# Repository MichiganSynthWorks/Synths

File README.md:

# Synths
Synth Related Projects

Bella: Synth based on the Mutable Instruments Anushri originally designed by Emilie Gillet

Xena: Synth based on the Mutable Instruments Ambika originally designed by Emilie Gillet

MIDIme: MIDI processor based on the Mutable Instruments MIDIpal originally designed by Emilie Gillet

UMR2 CSO1 Edition: Cusomized MIDI to keyboard adapter for the Yamaha CS-01.  UMR2 Orginally designed by John Staskevich

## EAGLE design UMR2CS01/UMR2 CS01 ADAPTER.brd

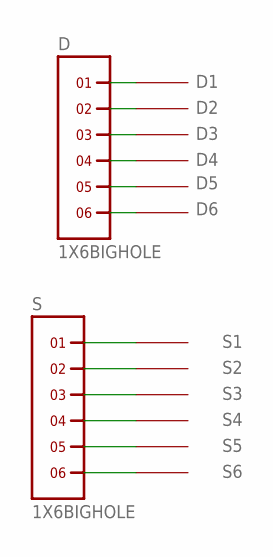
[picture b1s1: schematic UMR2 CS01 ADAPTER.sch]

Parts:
D: 1X6BIGHOLE; 1X6
D1, D2, D3, D4, D5, D6: SMD_PAD; SMDPAD_1X2
S: 1X6BIGHOLE; 1X6
S1, S2, S3, S4, S5, S6: SMD_PAD; SMDPAD_1X2

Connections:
unnamed: D.1, D1.P$1
unnamed: D.2, D2.P$1
unnamed: D.3, D3.P$1
unnamed: D.4, D4.P$1
unnamed: D.5, D5.P$1
unnamed: D.6, D6.P$1
unnamed: S.1, S1.P$1
unnamed: S.2, S2.P$1
unnamed: S.3, S3.P$1
unnamed: S.4, S4.P$1
unnamed: S.5, S5.P$1
unnamed: S.6, S6.P$1

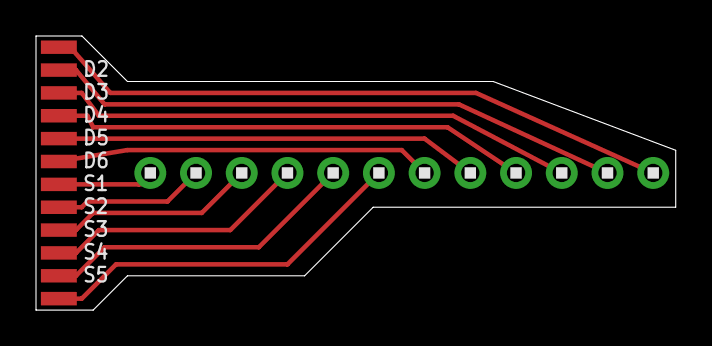
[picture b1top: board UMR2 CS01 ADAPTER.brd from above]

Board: 2 copper layers, 35.5 x 15.2 mm, 14 parts (0 on the bottom side), 12 nets.

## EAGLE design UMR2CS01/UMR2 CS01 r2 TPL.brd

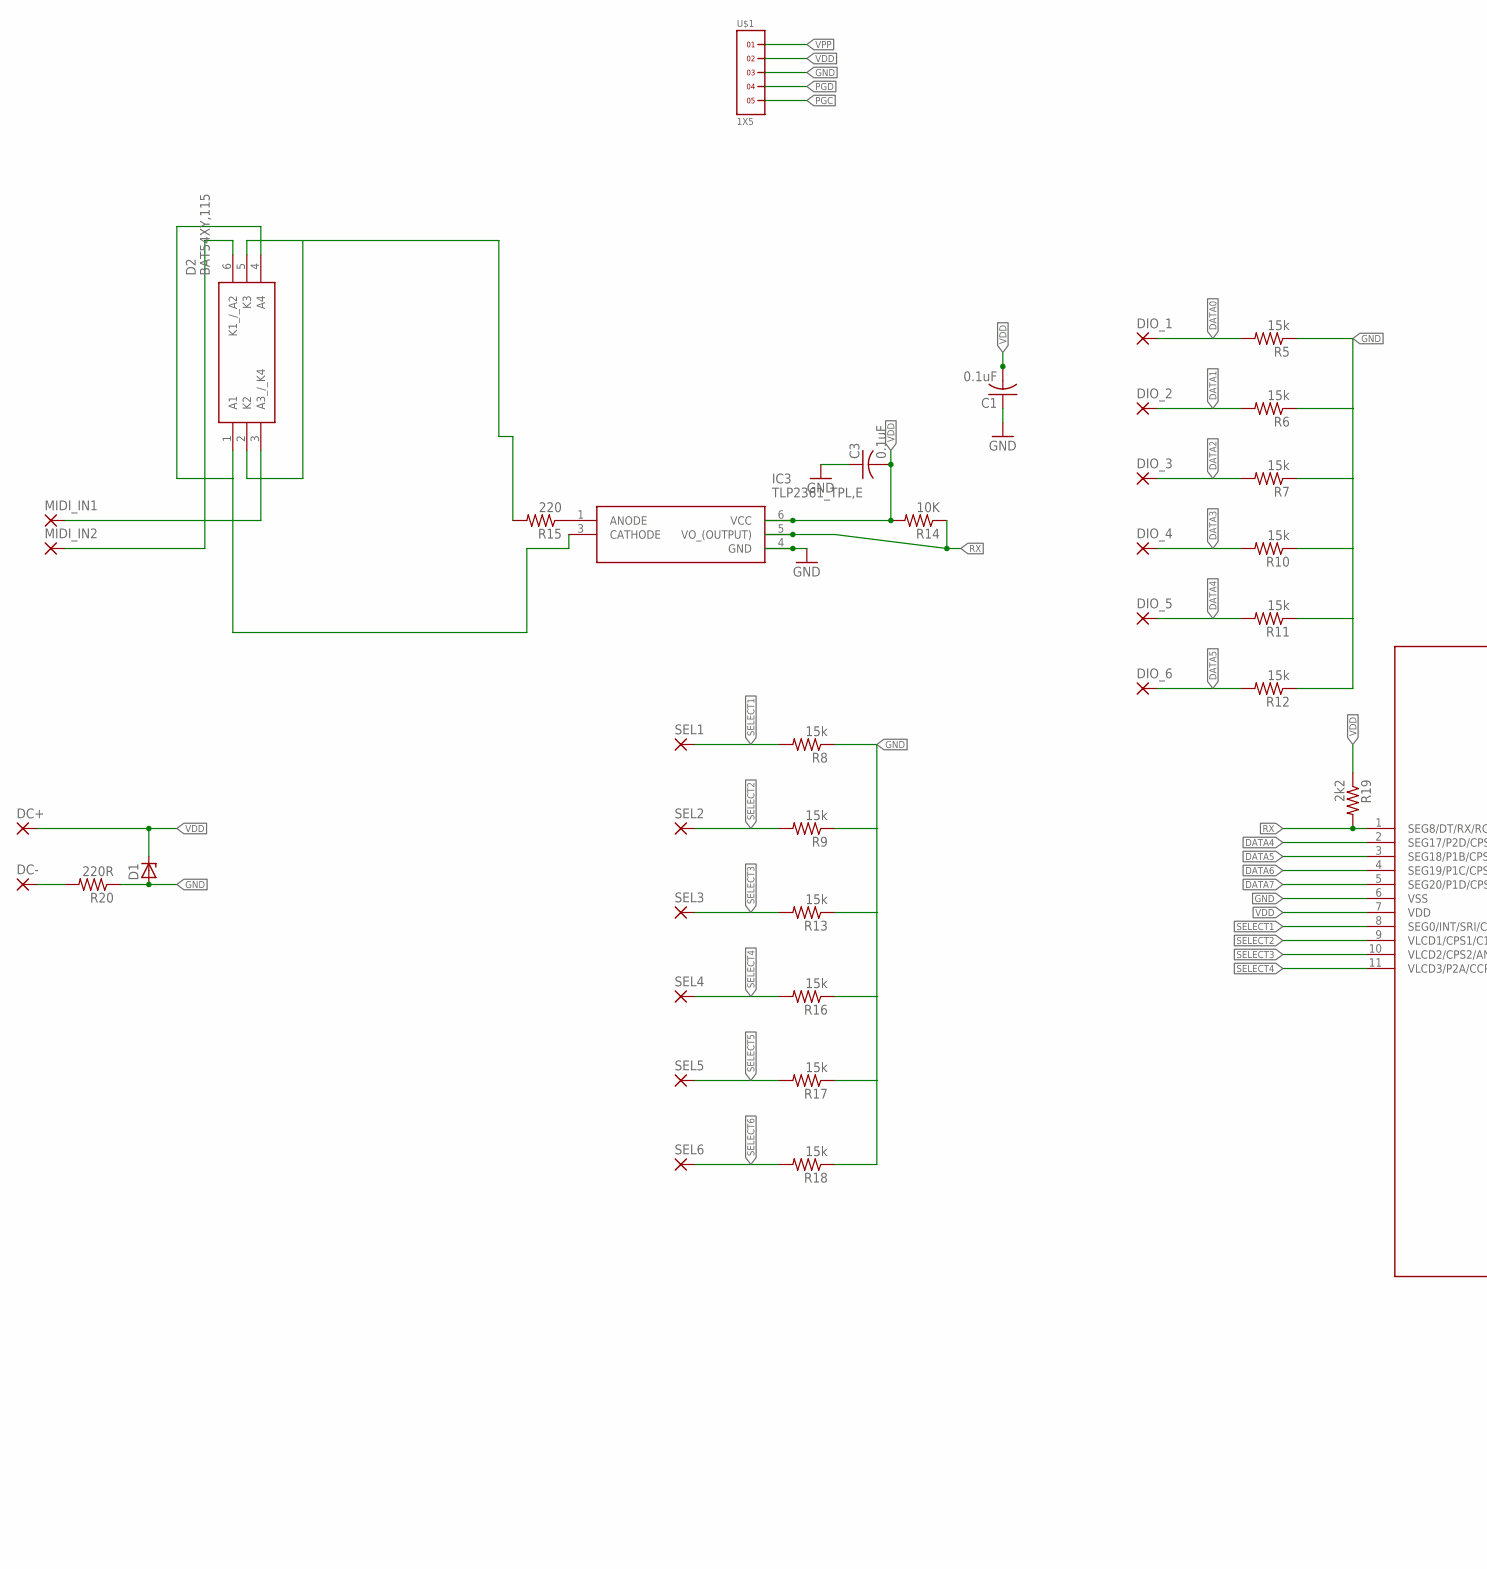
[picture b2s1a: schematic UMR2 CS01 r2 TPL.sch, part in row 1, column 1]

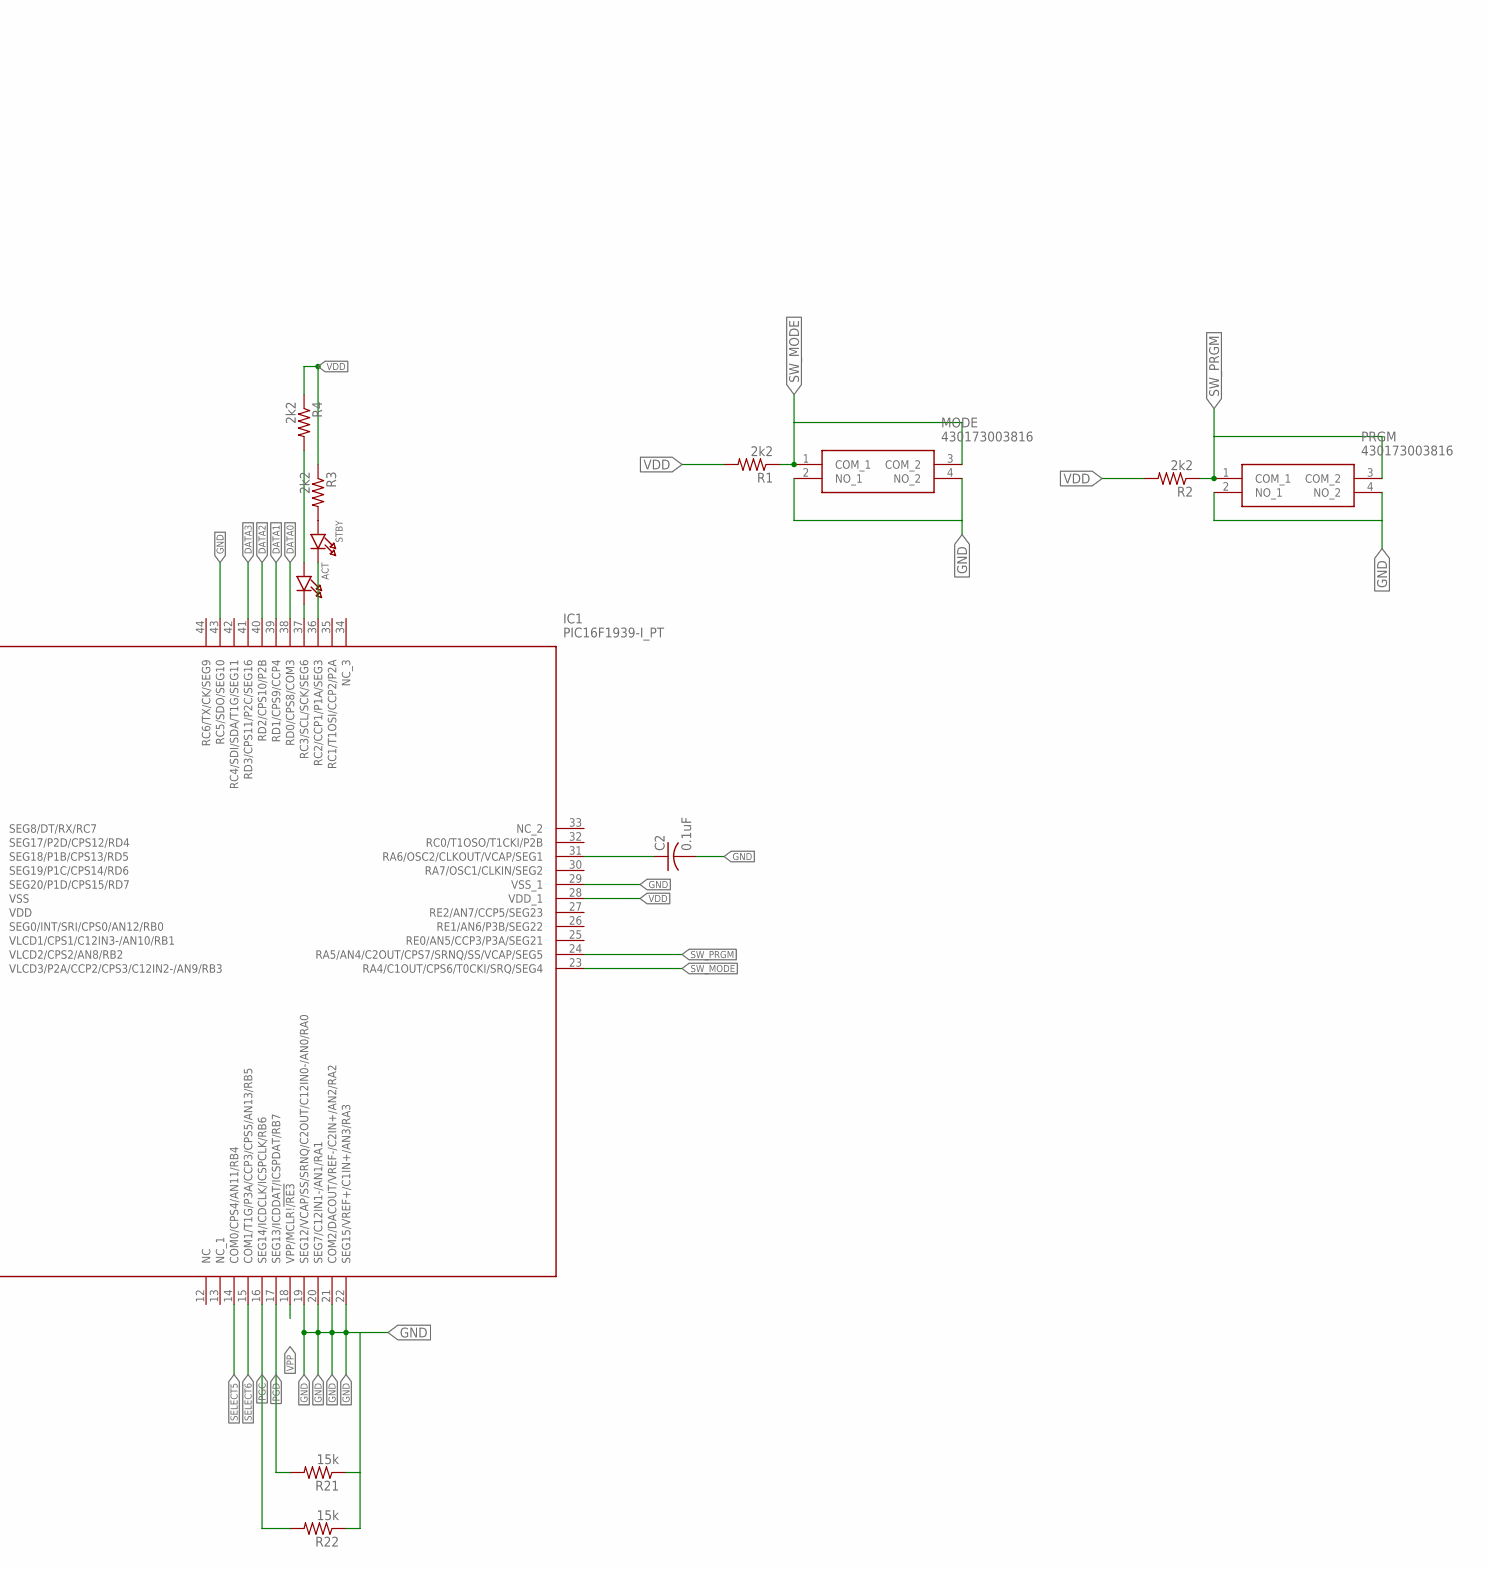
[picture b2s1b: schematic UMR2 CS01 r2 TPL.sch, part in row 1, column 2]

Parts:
ACT: LED0603_NOOUTLINE; CHIPLED_0603_NOOUTLINE
C1, C2, C3: 0.1uF; RCL_C0603
D1: ZENER_DIODESOD123; SOD123
D2: BAT54XY,115; SOT65P210X110-6N
DC+: SMD2; SMD1,27-2,54
DC-: SMD2; SMD1,27-2,54
DIO_1, DIO_2, DIO_3, DIO_4, DIO_5, DIO_6: SMD2; SMD1,27-2,54
IC1: PIC16F1939-I_PT; QFP80P1200X1200X120-44N
IC3: TLP2361_TPL,E; 11-4L1S(5-PIN-SOIC)
MIDI_IN1, MIDI_IN2: SMD2; SMD1,27-2,54
MODE: 430173003816
PRGM: 430173003816
R1, R2, R3, R4, R19: 2k2; RCL_R0603
R5, R6, R7, R8, R9, R10, R11, R12, R13, R16, R17, R18, R21, R22: 15k; RCL_R0603
R14: 10K; RCL_R0603
R15: 220; RCL_R0603
R20: 220R; RCL_R0603
SEL1, SEL2, SEL3, SEL4, SEL5, SEL6: SMD2; SMD1,27-2,54
STBY: LED0603_NOOUTLINE; CHIPLED_0603_NOOUTLINE
U$1: 1X5

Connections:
ACT: ACT.C, IC1.37 (RC3/SCL/SCK/SEG6)
DATA0: DIO_1.1, IC1.38 (RD0/CPS8/COM3), R5.2
DATA1: DIO_2.1, IC1.39 (RD1/CPS9/CCP4), R6.2
DATA2: DIO_3.1, IC1.40 (RD2/CPS10/P2B), R7.2
DATA3: DIO_4.1, IC1.41 (RD3/CPS11/P2C/SEG16), R10.2
DATA4: DIO_5.1, IC1.2 (SEG17/P2D/CPS12/RD4), R11.2
DATA5: DIO_6.1, IC1.3 (SEG18/P1B/CPS13/RD5), R12.2
DATA6: IC1.4 (SEG19/P1C/CPS14/RD6)
DATA7: IC1.5 (SEG20/P1D/CPS15/RD7)
GND: C1.1, C2.2, C3.1, D1.ANODE, IC1.6 (VSS), IC1.19 (SEG12/VCAP/SS/SRNQ/C2OUT/C12IN0-/AN0/RA0), IC1.20 (SEG7/C12IN1-/AN1/RA1), IC1.21 (COM2/DACOUT/VREF-/C2IN+/AN2/RA2), IC1.22 (SEG15/VREF+/C1IN+/AN3/RA3), IC1.29 (VSS_1), IC1.43 (RC5/SDO/SEG10), IC3.4 (GND), MODE.2 (NO_1), MODE.4 (NO_2), PRGM.2 (NO_1), PRGM.4 (NO_2), R5.1, R6.1, R7.1, R8.1, R9.1, R10.1, R11.1, R12.1, R13.1, R16.1, R17.1, R18.1, R20.1, R21.1, R22.1, U$1.3
MIDI_IN_RING: D2.6 (K1_/_A2), MIDI_IN2.1
MIDI_IN_TIP: D2.3 (A3_/_K4), MIDI_IN1.1
unnamed: IC3.1 (ANODE), R15.1
unnamed: D2.1 (A1), D2.4 (A4), IC3.3 (CATHODE)
unnamed: R3.2, STBY.A
unnamed: ACT.A, R4.2
unnamed: DC-.1, R20.2
unnamed: D2.2 (K2), D2.5 (K3), R15.2
PGC: IC1.16 (SEG14/ICDCLK/ICSPCLK/RB6), R22.2, U$1.5
PGD: IC1.17 (SEG13/ICDDAT/ICSPDAT/RB7), R21.2, U$1.4
RX: IC1.1 (SEG8/DT/RX/RC7), IC3.5 (VO_(OUTPUT)), R14.1, R19.2
SELECT1: IC1.8 (SEG0/INT/SRI/CPS0/AN12/RB0), R8.2, SEL1.1
SELECT2: IC1.9 (VLCD1/CPS1/C12IN3-/AN10/RB1), R9.2, SEL2.1
SELECT3: IC1.10 (VLCD2/CPS2/AN8/RB2), R13.2, SEL3.1
SELECT4: IC1.11 (VLCD3/P2A/CCP2/CPS3/C12IN2-/AN9/RB3), R16.2, SEL4.1
SELECT5: IC1.14 (COM0/CPS4/AN11/RB4), R17.2, SEL5.1
SELECT6: IC1.15 (COM1/T1G/P3A/CCP3/CPS5/AN13/RB5), R18.2, SEL6.1
STBY: IC1.36 (RC2/CCP1/P1A/SEG3), STBY.C
SW_MODE: IC1.23 (RA4/C1OUT/CPS6/T0CKI/SRQ/SEG4), MODE.1 (COM_1), MODE.3 (COM_2), R1.1
SW_PRGM: IC1.24 (RA5/AN4/C2OUT/CPS7/SRNQ/SS/VCAP/SEG5), PRGM.1 (COM_1), PRGM.3 (COM_2), R2.1
VCAP: C2.1, IC1.31 (RA6/OSC2/CLKOUT/VCAP/SEG1)
VDD: C1.2, C3.2, D1.CATHODE, DC+.1, IC1.7 (VDD), IC1.28 (VDD_1), IC3.6 (VCC), R1.2, R2.2, R3.1, R4.1, R14.2, R19.1, U$1.2
VPP: IC1.18 (VPP/MCLR!!/RE3), U$1.1

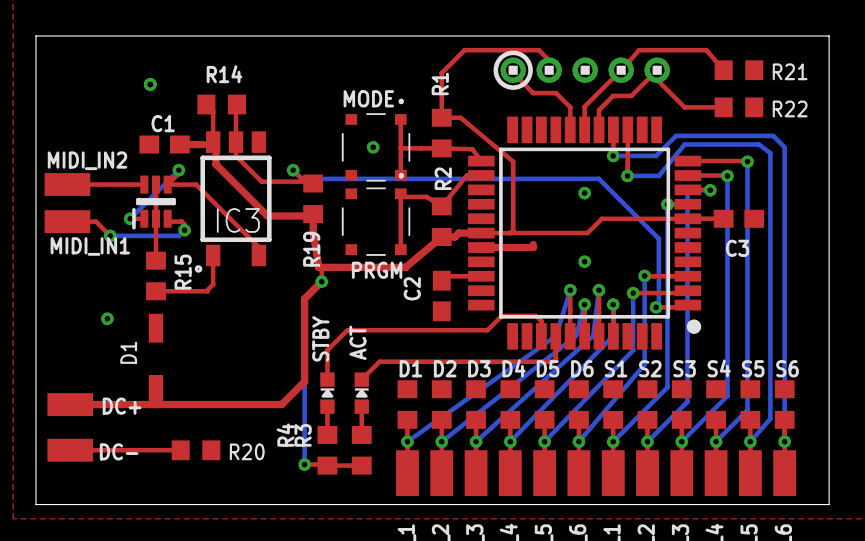
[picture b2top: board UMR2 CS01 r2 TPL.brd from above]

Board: 2 copper layers, 44.1 x 26.0 mm, 51 parts (0 on the bottom side), 31 nets.

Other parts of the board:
U$2: MSW_LOGO_0.5"

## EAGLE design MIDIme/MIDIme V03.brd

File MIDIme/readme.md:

7/17/24

Updated boards, case, and code

5/1/24

Initial Release

MIDIpal: MIDI processor based on the Mutable Instruments MIDIpal originally designed by Emilie Gillet

Original CAD file, PCB & Schematic and original design elements provided by Mutable Instruments under creative commons CC-BY-SA-3.0 license.
https://github.com/pichenettes/midipal

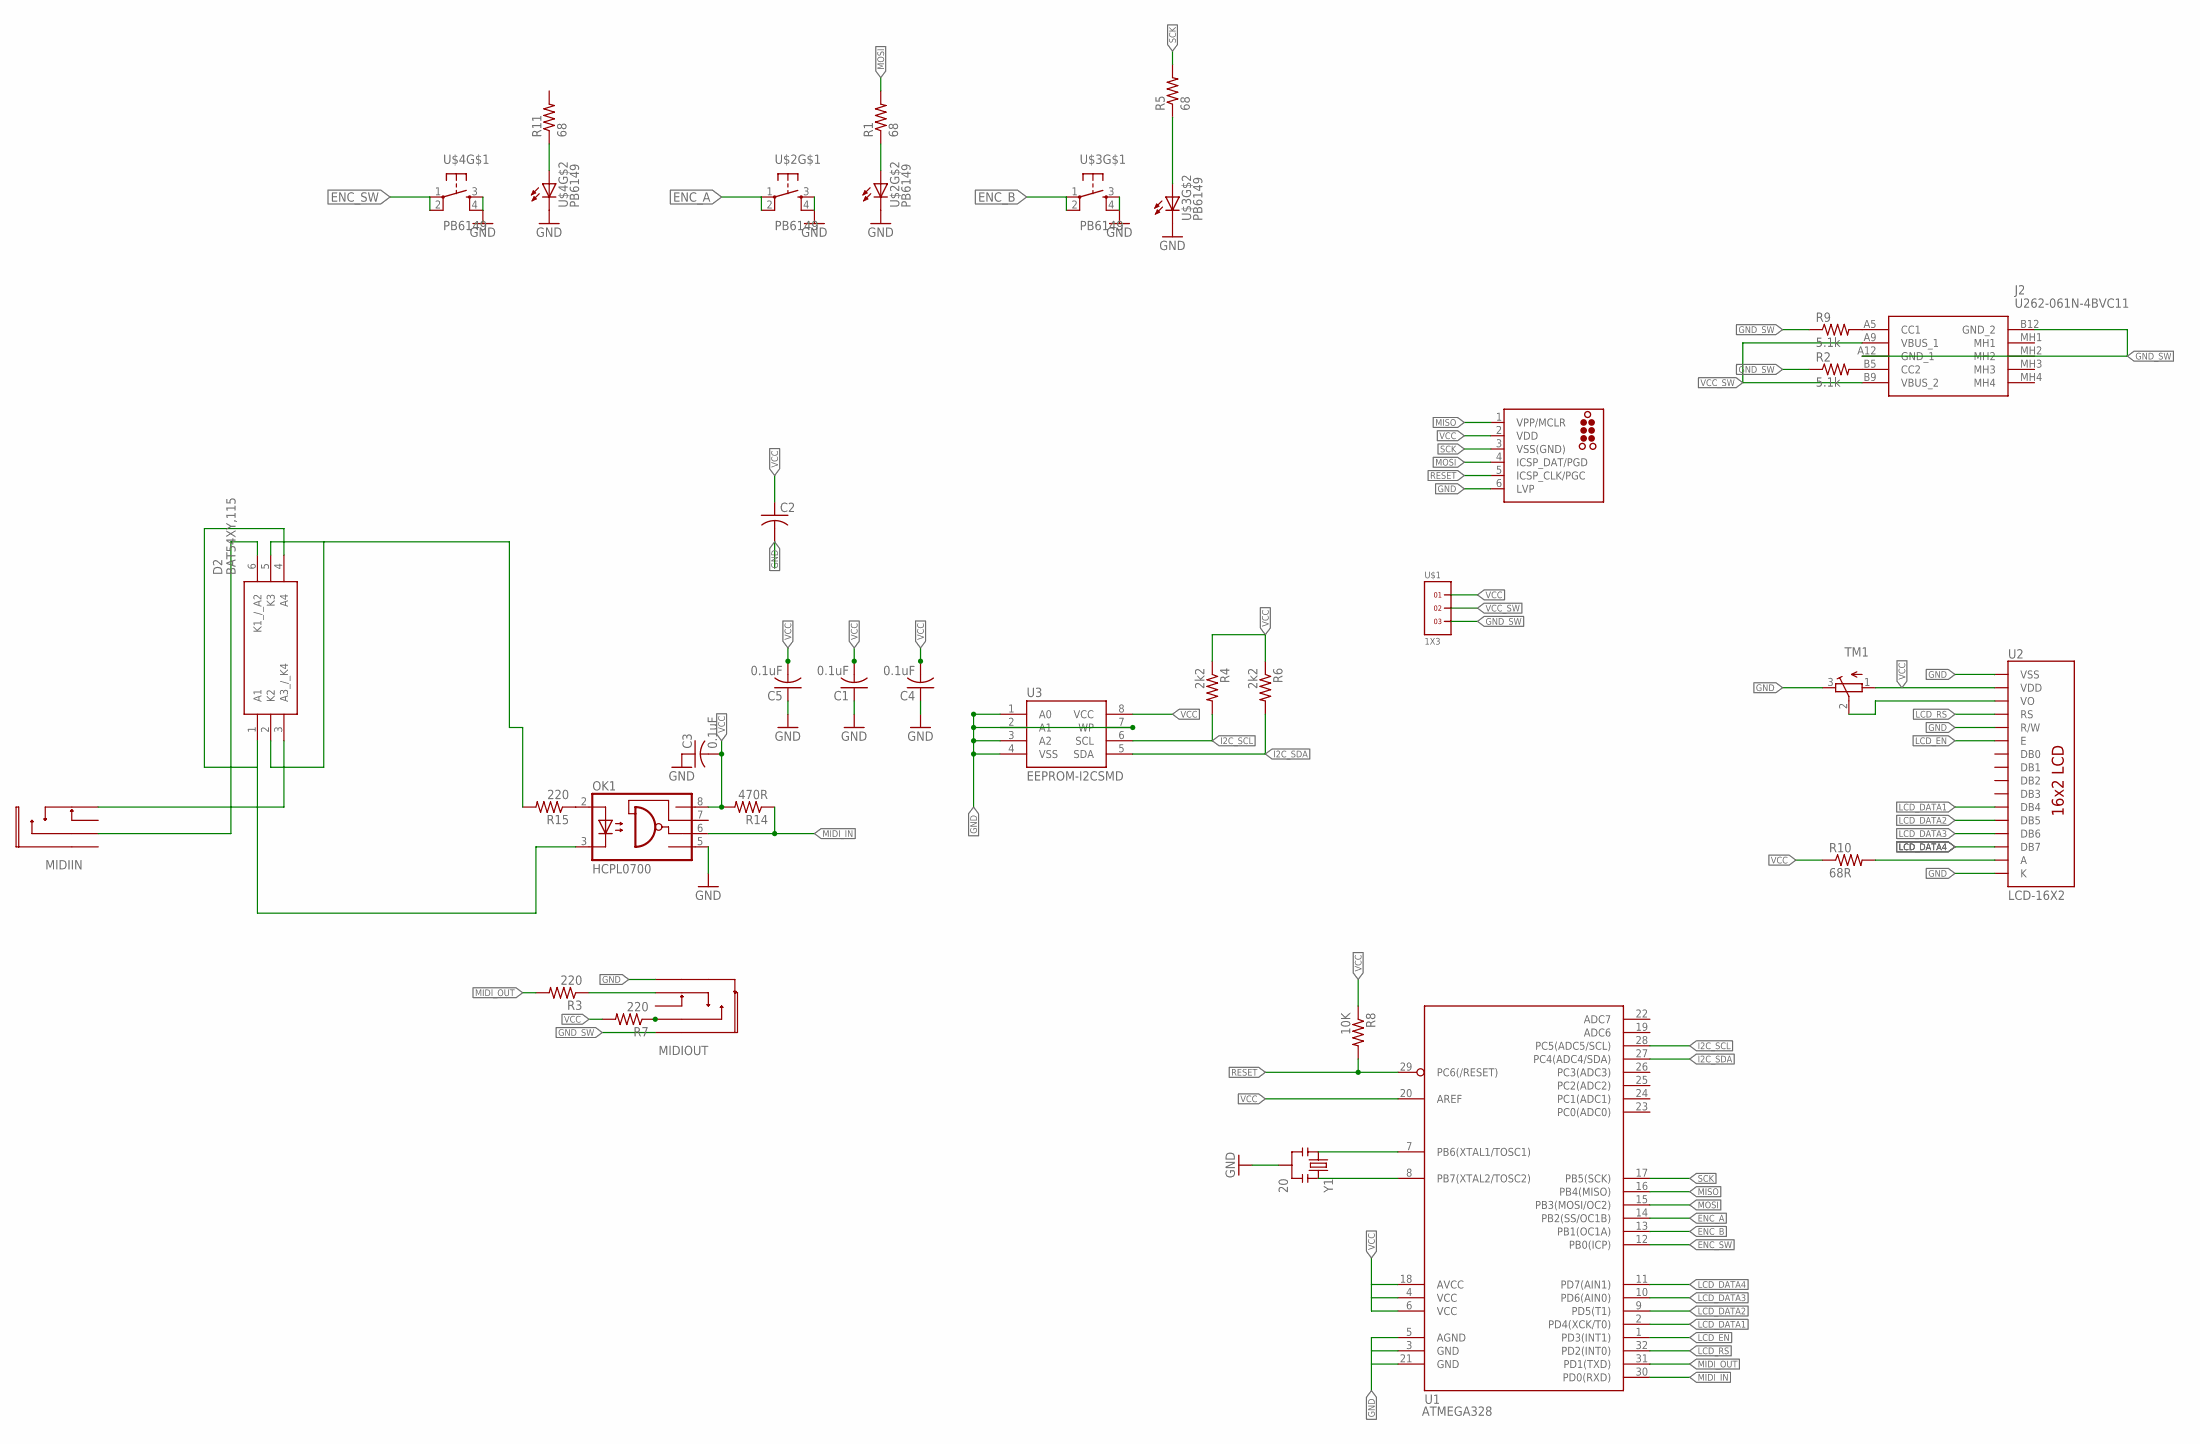
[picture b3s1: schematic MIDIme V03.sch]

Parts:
C1, C3, C4, C5: 0.1uF; RCL_C0402K
C2: C-USC0805K; C0805K
D2: BAT54XY,115; SOT65P210X110-6N
J2: U262-061N-4BVC11; USB4125GFA
J5: TC2030-MCP-NL
MIDIIN: PJ327E; PJ327
MIDIOUT: PJ327E_GSW; PJ327A_5A
OK1: HCPL0700; SOIC08
R1, R5, R11: 68; R0402
R2, R9: 5.1k; R0402
R3, R7, R15: 220; RCL_R0402
R4, R6: 2k2; RCL_R0402
R8: 10K; RCL_R0402
R10: 68R; RCL_R0402
R14: 470R; RCL_R0402
TM1: TRIMPOTTC33X; TC33X
U1: ATMEGA328; TQFP32-08
U2: LCD-16X2; LCD-8X2_NOHOLE
U3: EEPROM-I2CSMD; SO08
U$1: 1X3
U$2, U$3, U$4: PB6149
Y1: 20; RESONATOR-SMD

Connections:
ENC_A: U1.14 (PB2(SS/OC1B)), U$2.1, U$2.2
ENC_B: U1.13 (PB1(OC1A)), U$3.1, U$3.2
ENC_SW: U1.12 (PB0(ICP)), U$4.1, U$4.2
GND: C1.1, C2.2, C3.1, C4.1, C5.1, J5.6 (LVP), MIDIOUT.P$4, OK1.5 (GND), TM1.3 (E), U1.3 (GND), U1.5 (AGND), U1.21 (GND), U2.1 (VSS), U2.5 (R/W), U2.16 (K), U3.1 (A0), U3.2 (A1), U3.3 (A2), U3.4 (VSS), U3.7 (WP), U$2.3, U$2.4, U$2.5 (C), U$3.3, U$3.4, U$3.5 (C), U$4.3, U$4.4, U$4.5 (C), Y1.2
GND_SW: J2.A12 (GND_1), J2.B12 (GND_2), MIDIOUT.P$1, R2.1, R9.1, U$1.3
I2C_SCL: R4.2, U1.28 (PC5(ADC5/SCL)), U3.6 (SCL)
I2C_SDA: R6.2, U1.27 (PC4(ADC4/SDA)), U3.5 (SDA)
LCD_DATA1: U1.2 (PD4(XCK/T0)), U2.11 (DB4)
LCD_DATA2: U1.9 (PD5(T1)), U2.12 (DB5)
LCD_DATA3: U1.10 (PD6(AIN0)), U2.13 (DB6)
LCD_DATA4: U1.11 (PD7(AIN1)), U2.14 (DB7)
LCD_EN: U1.1 (PD3(INT1)), U2.6 (E)
LCD_RS: U1.32 (PD2(INT0)), U2.4 (RS)
MIDI_IN: OK1.6 (VO), R14.1, U1.30 (PD0(RXD))
MIDI_IN_RING: D2.6 (K1_/_A2), MIDIIN.P$3
MIDI_IN_TIP: D2.3 (A3_/_K4), MIDIIN.P$2
MIDI_OUT: R3.2, U1.31 (PD1(TXD))
MISO: J5.1 (VPP/MCLR), U1.16 (PB4(MISO))
MOSI: J5.4 (ICSP_DAT/PGD), R1.2, U1.15 (PB3(MOSI/OC2))
unnamed: R5.1, U$3.6 (A)
unnamed: U1.7 (PB6(XTAL1/TOSC1)), Y1.1
unnamed: D2.1 (A1), D2.4 (A4), OK1.3 (C)
unnamed: J2.B5 (CC2), R2.2
unnamed: U1.8 (PB7(XTAL2/TOSC2)), Y1.3
unnamed: J2.A5 (CC1), R9.2
unnamed: MIDIOUT.P$3, R7.1
unnamed: MIDIOUT.P$2, R3.1
unnamed: R1.1, U$2.6 (A)
unnamed: TM1.2 (S), U2.3 (VO)
unnamed: R10.2, U2.15 (A)
unnamed: R11.1, U$4.6 (A)
unnamed: OK1.2 (A), R15.1
unnamed: D2.2 (K2), D2.5 (K3), R15.2
RESET: J5.5 (ICSP_CLK/PGC), R8.2, U1.29 (PC6(/RESET))
SCK: J5.3 (VSS(GND)), R5.2, U1.17 (PB5(SCK))
VCC: C1.2, C2.1, C3.2, C4.2, C5.2, J5.2 (VDD), OK1.8 (VCC), R4.1, R6.1, R7.2, R8.1, R10.1, R14.2, TM1.1 (A), U1.4 (VCC), U1.6 (VCC), U1.18 (AVCC), U1.20 (AREF), U2.2 (VDD), U3.8 (VCC), U$1.1
VCC_SW: J2.A9 (VBUS_1), J2.B9 (VBUS_2), U$1.2

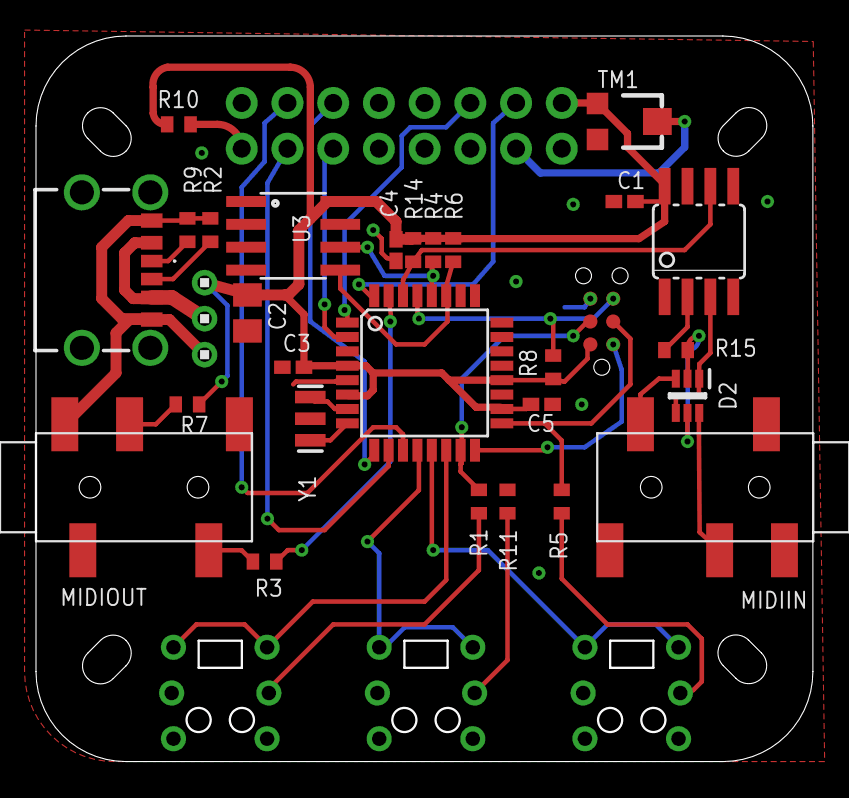
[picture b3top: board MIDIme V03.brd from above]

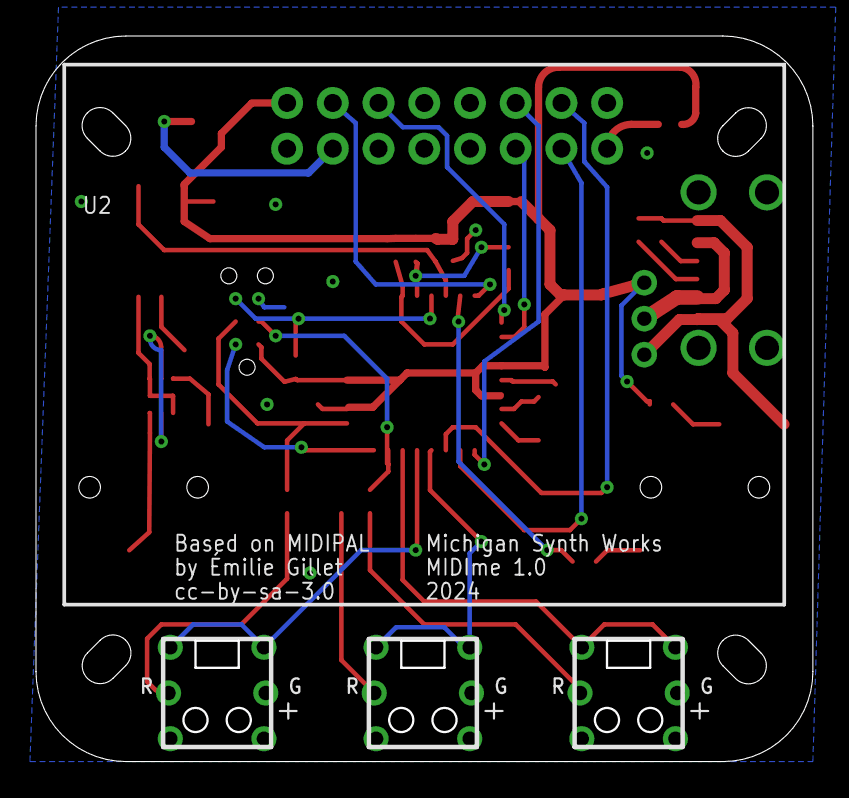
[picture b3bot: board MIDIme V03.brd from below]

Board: 2 copper layers, 43.0 x 40.2 mm, 33 parts (4 on the bottom side), 37 nets.

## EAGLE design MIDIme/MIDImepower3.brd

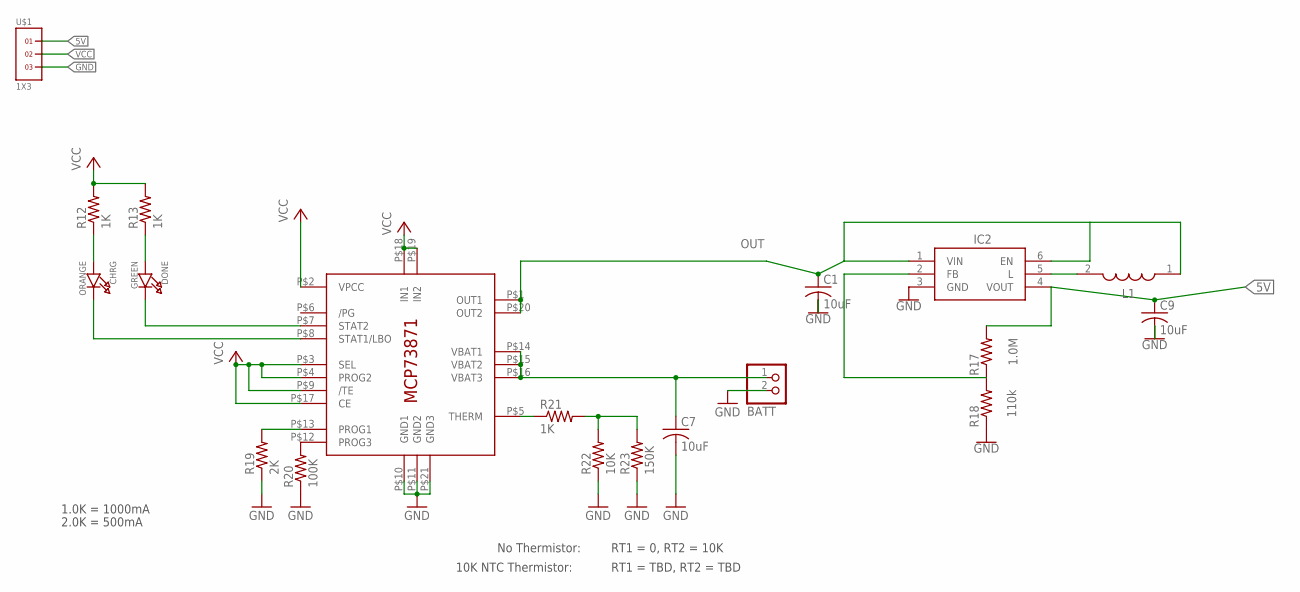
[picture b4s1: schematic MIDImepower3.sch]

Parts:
BATT: JST_2PIN-SMT-RA; JST-PH-2-SMT-RA
C1, C7, C9: 10uF; C0805K
CHRG: ORANGE; CHIPLED_0805_NOOUTLINE
DONE: GREEN; CHIPLED_0805_NOOUTLINE
IC1: MCP73871; QFN20_4MM
IC2: TPS61220DCKT; SOT65P210X110-6N
L1: EPL3015-472MLC; EPL3015472MLC
R12, R13, R21: 1K; R0402
R17: 1.0M; R0402
R18: 110k; R0402
R19: 2K; R0402
R20: 100K; R0402
R22: 10K; R0402
R23: 150K; R0402
U$1: 1X3

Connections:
5V: C9.1, IC2.4 (VOUT), R17.2, U$1.1
BAT: BATT.1 (2), C7.1, IC1.P$14 (VBAT1), IC1.P$15 (VBAT2), IC1.P$16 (VBAT3)
GND: BATT.2 (1), C1.2, C7.2, C9.2, IC1.P$10 (GND1), IC1.P$11 (GND2), IC1.P$21 (GND3), IC2.3 (GND), R18.1, R19.1, R20.1, R22.1, R23.1, U$1.3
unnamed: DONE.C, IC1.P$7 (STAT2)
unnamed: IC2.2 (FB), R17.1, R18.2
unnamed: IC2.5 (L), L1.2
unnamed: CHRG.C, IC1.P$8 (STAT1/LBO)
unnamed: CHRG.A, R12.1
unnamed: DONE.A, R13.1
unnamed: IC1.P$12 (PROG3), R20.2
unnamed: IC1.P$13 (PROG1), R19.2
unnamed: IC1.P$5 (THERM), R21.1
unnamed: R21.2, R22.2, R23.2
OUT: C1.1, IC1.P$1 (OUT1), IC1.P$20 (OUT2), IC2.1 (VIN), IC2.6 (EN), L1.1
VCC: IC1.P$2 (VPCC), IC1.P$3 (SEL), IC1.P$4 (PROG2), IC1.P$9 (/TE), IC1.P$17 (CE), IC1.P$18 (IN1), IC1.P$19 (IN2), R12.2, R13.2, U$1.2

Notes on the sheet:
1.0K = 1000mA
2.0K = 500mA
No Thermistor:
10K NTC Thermistor:
RT1 = 0, RT2 = 10K
RT1 = TBD, RT2 = TBD

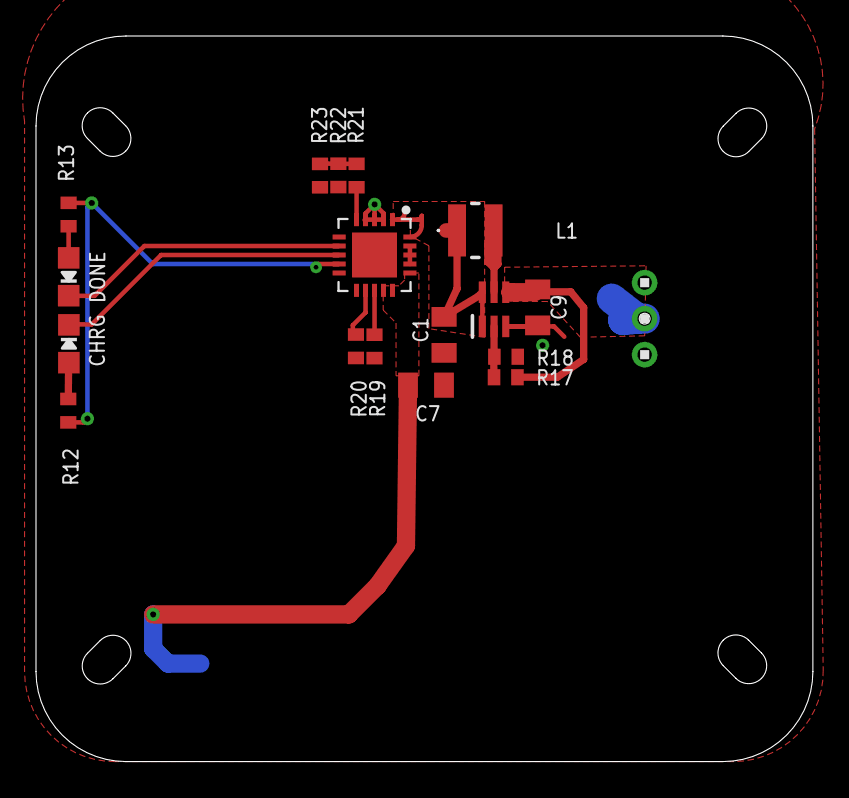
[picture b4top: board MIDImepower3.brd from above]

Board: 2 copper layers, 43.2 x 40.3 mm, 19 parts (1 on the bottom side), 15 nets.

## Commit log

2024-01-16 Add files via upload
    Added Voice Card Board Template
2024-07-17 Customized MIDIme code
2024-07-17 remove old ver
2025-08-08 Create readme.doc
    UMR2 CS01 Variant. MIDI to Keyboard adapter

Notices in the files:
UMR2CS01/UMR2 CS01 r2 TPL.brd:
CC by 4.0
parts and their libraries:
SparkFun-Displays: Licensing: CC v3.0 Share-Alike You are welcome to use this library for commercial purposes.
tag-connect: ©2009 ROFA.cz - modified and updated by Robert Darlington ‹rdarlington@gmail.com›
